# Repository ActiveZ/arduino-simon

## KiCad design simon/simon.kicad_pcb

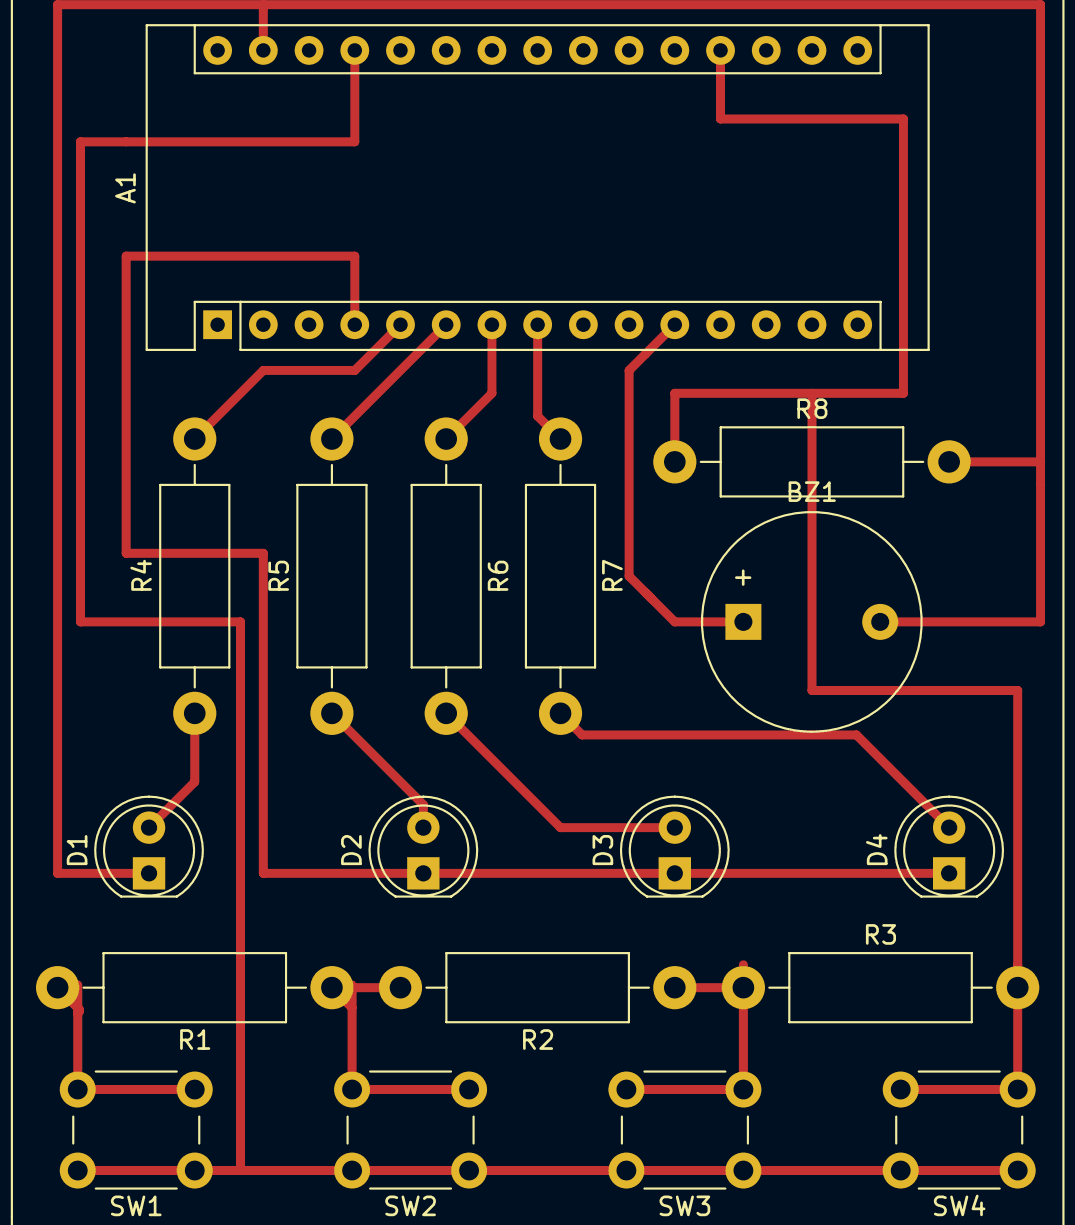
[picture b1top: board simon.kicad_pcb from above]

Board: 2 copper layers, 18 parts (0 on the bottom side), 15 nets.

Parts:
A1: Arduino_Nano_v3.x; Arduino_Nano
BZ1: Buzzer; Buzzer_12x9.5RM7.6
D1, D2, D3, D4: LED; LED_D5.0mm
R1, R2, R3, R4, R5, R6, R7: 220; R_Axial_DIN0411_L9.9mm_D3.6mm_P15.24mm_Horizontal
R8: 10k; R_Axial_DIN0411_L9.9mm_D3.6mm_P15.24mm_Horizontal
SW1, SW2, SW3, SW4: SW_Push; SW_PUSH_6mm_H5mm

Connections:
GND: A1.4, A1.29, BZ1.2, D1.1, D2.1, D3.1, D4.1, R8.2
unnamed: A1.5, R4.2
unnamed: A1.6, R5.2
unnamed: A1.7, R6.1
unnamed: A1.8, R7.1
unnamed: A1.11, BZ1.1
unnamed: A1.19, R3.2, R8.1, SW4.2
unnamed: A1.27, SW1.1, SW2.1, SW3.1, SW4.1
unnamed: D1.2, R4.1
unnamed: D2.2, R5.1
unnamed: D3.2, R6.2
unnamed: D4.2, R7.2
unnamed: R1.1, R2.2, SW2.2
unnamed: R1.2, SW1.2
unnamed: R2.1, R3.1, SW3.2

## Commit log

2020-06-25 install
